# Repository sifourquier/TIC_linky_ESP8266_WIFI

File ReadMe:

Si vous voulez reproduire se montage contacter moi d'abord en ouvrant une issue

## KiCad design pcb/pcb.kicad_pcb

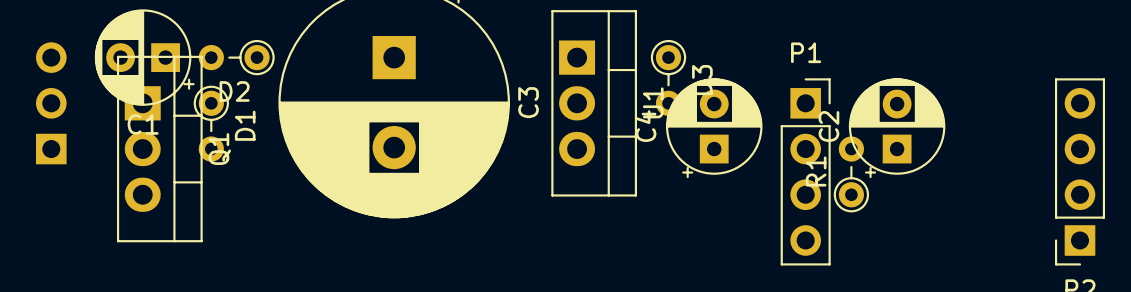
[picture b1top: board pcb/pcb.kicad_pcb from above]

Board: 2 copper layers, 13 parts (1 on the bottom side), 7 nets, no tracks yet.

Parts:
C1, C4: C; CP_Radial_D5.0mm_P2.50mm
C2: 1nF; CP_Radial_D5.0mm_P2.50mm
C3: 1000uF; CP_Radial_D12.5mm_P5.00mm
D1, D2: D; R_Axial_DIN0204_L3.6mm_D1.6mm_P2.54mm_Vertical
D3: 20V; R_Axial_DIN0204_L3.6mm_D1.6mm_P2.54mm_Vertical
J1: Conn_01x03_Male; PinSocket_1x03_P2.54mm_Horizontal
P1, P2: CONN_01X04; PinSocket_1x04_P2.54mm_Vertical
Q1: Q_NMOS_GDS; TO-220-3_Vertical
R1: 10k; R_Axial_DIN0204_L3.6mm_D1.6mm_P2.54mm_Vertical
U1: 3.3v; TO-220-3_Vertical

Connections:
+2V5: C4.1, P1.4, P2.1, P2.3, R1.1, U1.3
/A: C1.2, J1.3
/I2: J1.2, Q1.1
/RX: C2.1, P1.2, Q1.2, R1.2
GND: C2.2, C3.2, C4.2, D1.2, D3.2, J1.1, P1.1, Q1.3, U1.2
unnamed: C1.1, D1.1, D2.2
unnamed: C3.1, D2.1, D3.1, U1.1

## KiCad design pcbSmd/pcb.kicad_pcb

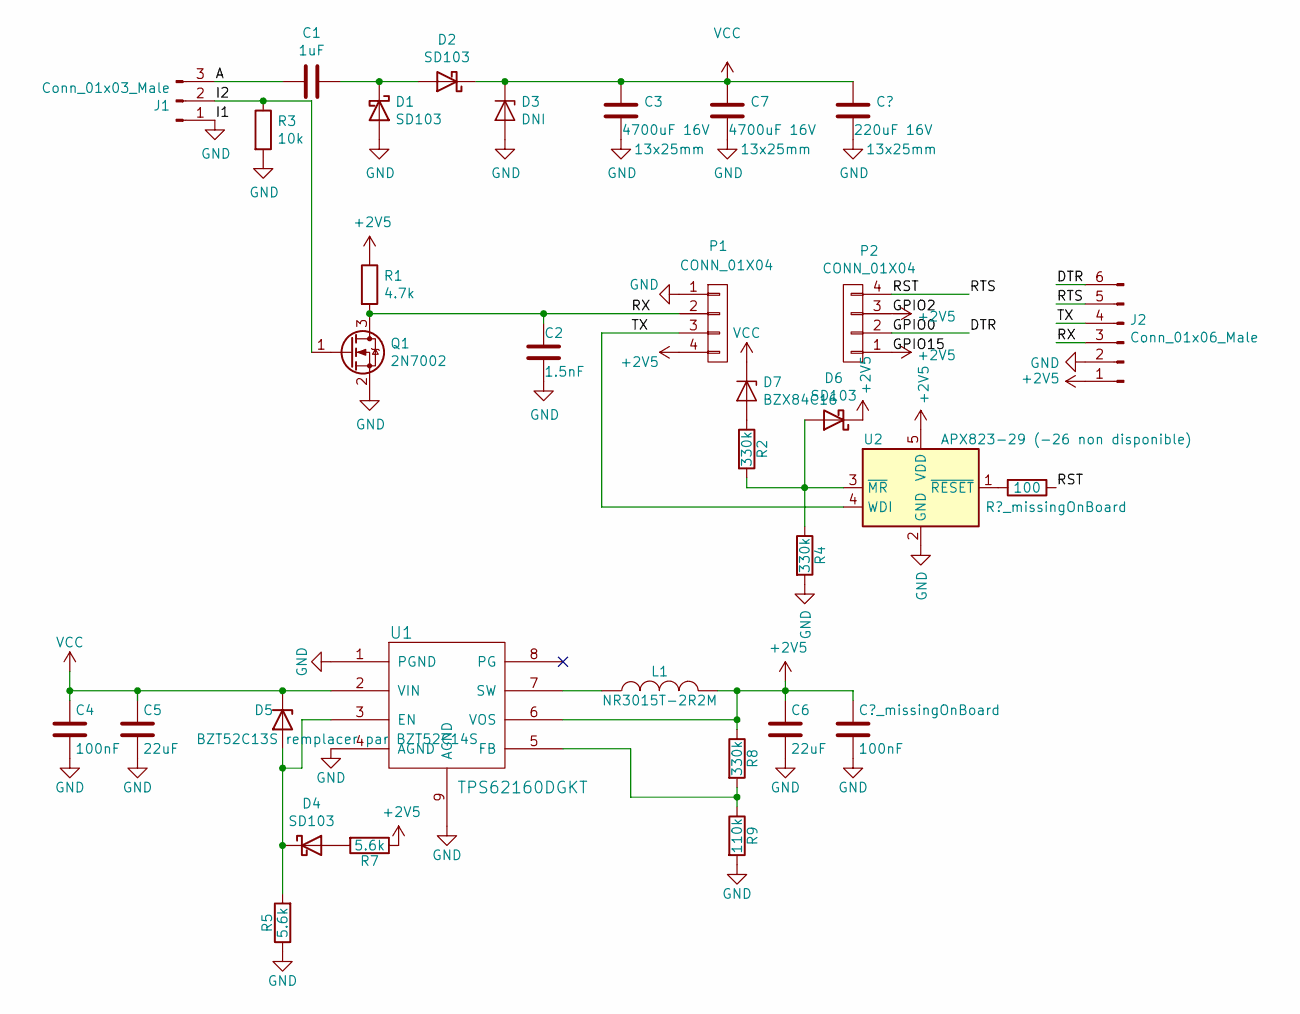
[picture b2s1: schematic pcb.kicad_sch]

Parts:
C1: 1uF; C_0805_2012Metric_Pad1.18x1.45mm_HandSolder
C2: 1.5nF; C_0603_1608Metric_Pad1.08x0.95mm_HandSolder
C3, C7: 4700uF 16V; CP_Radial_D12.5mm_P5.00mm
C4: 100nF; C_0603_1608Metric_Pad1.08x0.95mm_HandSolder
C5, C6: 22uF; C_0603_1608Metric_Pad1.08x0.95mm_HandSolder
C?_missingOnBoard: 100nF; C_0603_1608Metric_Pad1.08x0.95mm_HandSolder
D1, D2, D4, D6: SD103; D_SOD-323
D3: DNI; D_SOT-23_ANK
D5: BZT52C13S remplacer par BZT52C14S; D_SOD-323
D7: BZX84C16; D_SOT-23_ANK
J1: Conn_01x03_Male; PhoenixContact_MCV_1,5_3-G-5.08_1x03_P5.08mm_Vertical
J2: Conn_01x06_Male; PinHeader_1x06_P2.54mm_Vertical
L1: NR3015T-2R2M; L_Taiyo-Yuden_NR-30xx
P1, P2: CONN_01X04; PinSocket_1x04_P2.54mm_Vertical
Q1: 2N7002; SOT-23
R1: 4.7k; R_0603_1608Metric_Pad0.98x0.95mm_HandSolder
R2, R4, R8: 330k; R_0603_1608Metric_Pad0.98x0.95mm_HandSolder
R3: 10k; R_0603_1608Metric_Pad0.98x0.95mm_HandSolder
R5, R7: 5.6k; R_0603_1608Metric_Pad0.98x0.95mm_HandSolder
R9: 110k; R_0603_1608Metric_Pad0.98x0.95mm_HandSolder
R?_missingOnBoard: 100; R_0603_1608Metric_Pad0.98x0.95mm_HandSolder
U1: TPS62160DGKT; MSOP-8-1EP_3x3mm_P0.65mm_EP1.68x1.88mm_ThermalVias
U2: APX823-29 (-26 non disponible); SOT-23-5

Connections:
+2V5: C6.1, C?_missingOnBoard.1, D6.1 (K), J2.1, L1.2, P1.4, P2.1, P2.3, R1.1, R7.1, R8.1, U1.6 (VOS), U2.5 (VDD)
/A: C1.2, J1.3
/CTS: J2.6, P2.2
/I2: J1.2, Q1.1 (G), R3.1
/RST: J2.5, P2.4, R?_missingOnBoard.1, R?_missingOnBoard.2, U2.1 (~RESET)
/RX: C2.1, J2.3, P1.2, Q1.3 (D), R1.2
/TX: J2.4, P1.3, U2.4 (WDI)
GND: C2.2, C3.2, C4.2, C5.2, C6.2, C7.2, D1.2 (A), D3.2 (A), J1.1, J2.2, P1.1, Q1.2 (S), R3.2, R4.2, R5.1, R9.2, U1.1 (PGND), U1.4 (AGND), U1.9 (AGND), U2.2 (GND)
unnamed: C1.1, D1.1 (K), D2.2 (A)
unnamed: D4.1 (K), D5.2 (A), R5.2, U1.3 (EN)
unnamed: D4.2 (A), R7.2
unnamed: D6.2 (A), R2.2, R4.1, U2.3 (~MR)
unnamed: D7.2 (A), R2.1
unnamed: L1.1, U1.7 (SW)
unnamed: R8.2, R9.1, U1.5 (FB)
VCC: C3.1, C4.1, C5.1, C7.1, D2.1 (K), D3.1 (K), D5.1 (K), D7.1 (K), U1.2 (VIN)

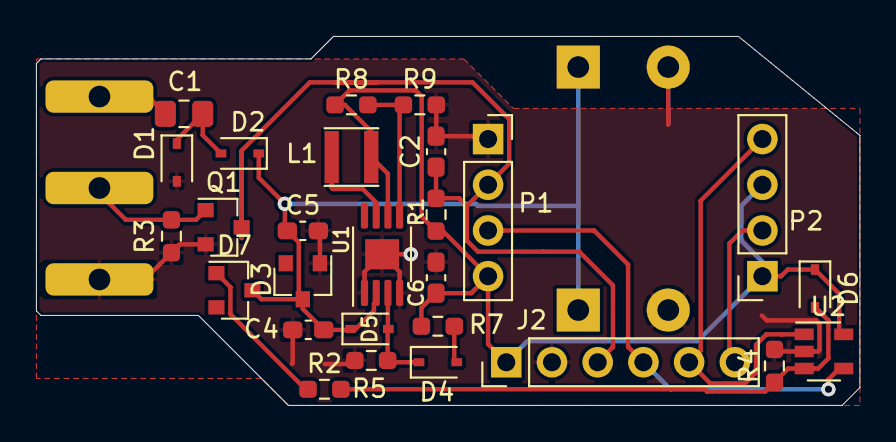
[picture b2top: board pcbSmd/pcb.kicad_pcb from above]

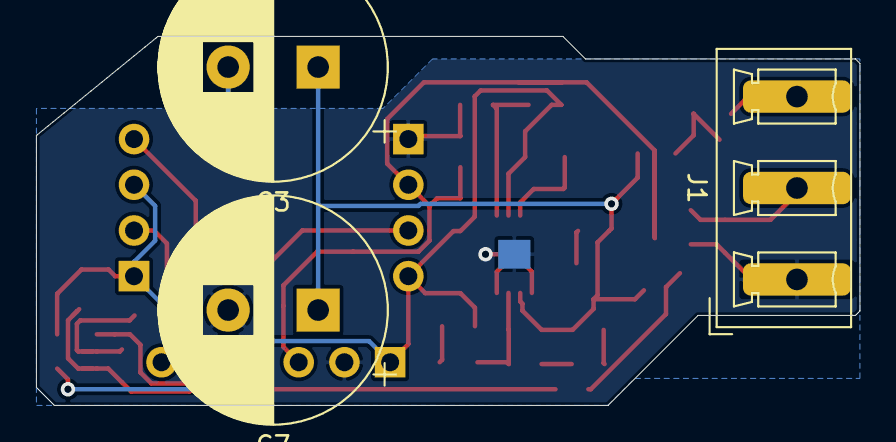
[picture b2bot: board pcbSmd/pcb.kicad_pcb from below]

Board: 2 copper layers, 45.8 x 20.5 mm, 30 parts (3 on the bottom side), 16 nets.

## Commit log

2023-06-20 je sais plus
2025-04-04 Quelque correction de valeur.
